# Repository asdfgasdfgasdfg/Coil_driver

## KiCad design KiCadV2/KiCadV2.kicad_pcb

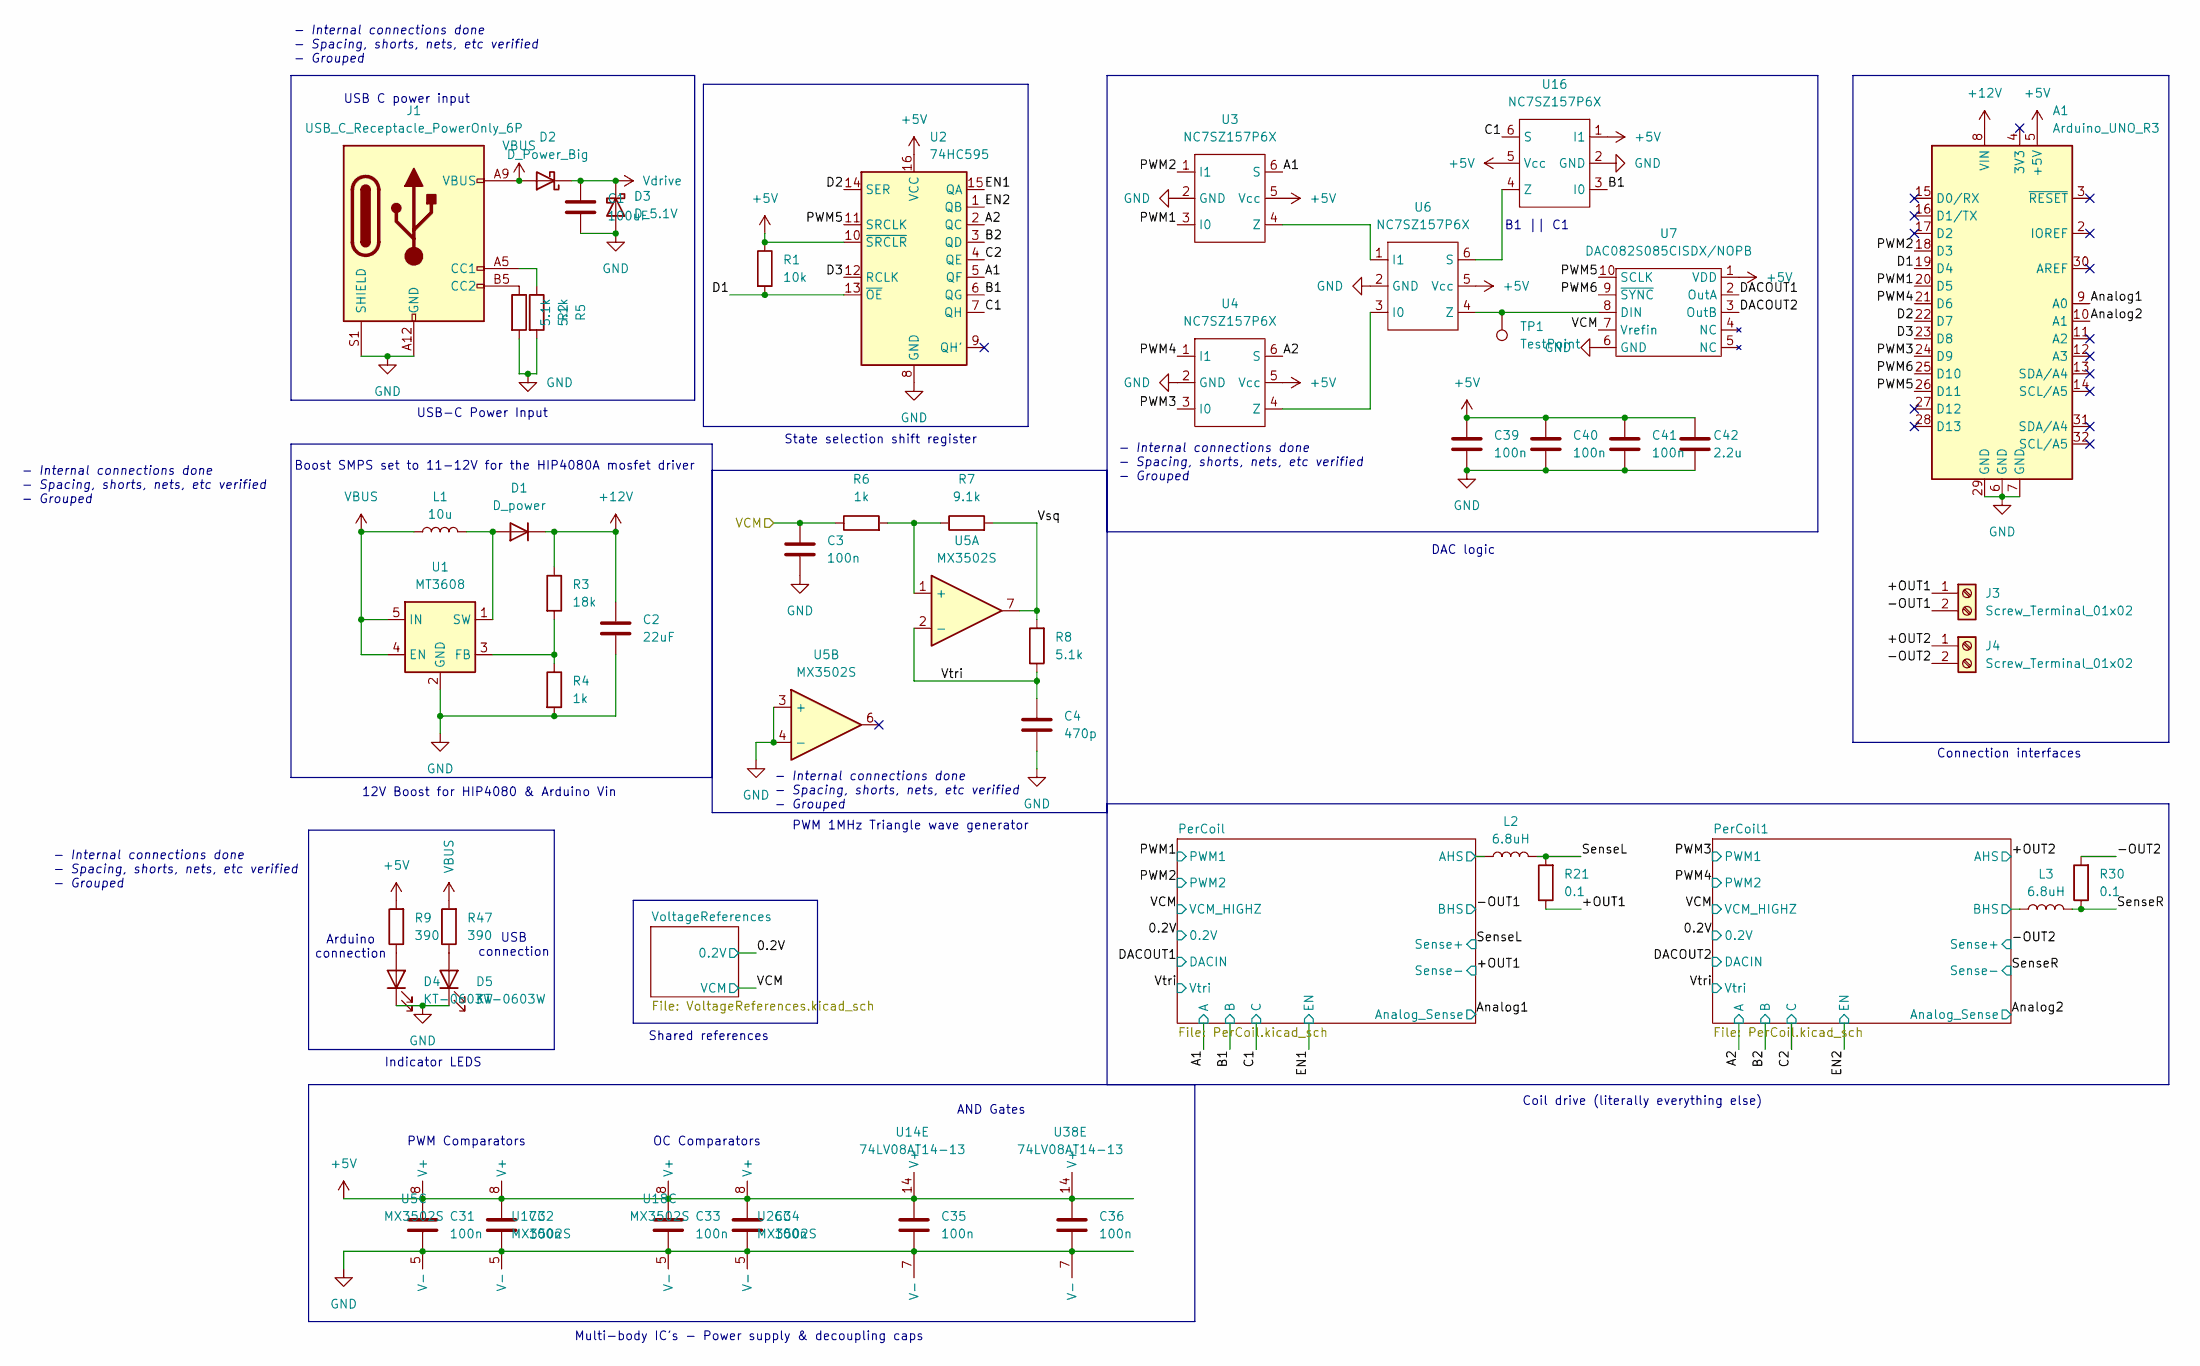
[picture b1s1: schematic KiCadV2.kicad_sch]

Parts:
A1: Arduino_UNO_R3; Arduino_UNO_R3_ConnOnly_Coil_Driver
C1: 100uF; C_1206_3216Metric; LCSC C15008
C2: 22uF; C_1206_3216Metric; LCSC C12891
C3, C31, C32, C33, C34, C35, C36, C39, C40, C41: 100n; C_0603_1608Metric; LCSC C14663
C4: 470p; C_0603_1608Metric; LCSC C396711
C42: 2.2u; C_0603_1608Metric; LCSC C23630
D1: D_power; D_SOD-123; LCSC C8598
D2: D_Power_Big; D_SMC; LCSC C18199212
D3: D_5.1V; D_SMB; LCSC C19077494
D4, D5: KT-0603W; LED_0603_1608Metric; LCSC C2290
J1: USB_C_Receptacle_PowerOnly_6P; USB_C_Receptacle_GCT_USB4135-GF-A_6P_TopMnt_Horizontal; LCSC C2927028
J3, J4: Screw_Terminal_01x02; PinHeader_2x01_P2.54mm_Vertical
L1: 10u; 10uH C15029; LCSC C15029
L2, L3: 6.8uH; 6.8uH C5127257; LCSC C5127257
R1: 10k; R_0603_1608Metric; LCSC C25804
R2, R5, R8: 5.1k; R_0603_1608Metric; LCSC C23186
R3: 18k; R_0603_1608Metric; LCSC C25810
R4, R6: 1k; R_0603_1608Metric; LCSC C21190
R7: 9.1k; R_0603_1608Metric; LCSC C23260
R9, R47: 390; R_0603_1608Metric; LCSC C23151
R21, R30: 0.1; R_1206_3216Metric; LCSC C42460614
TP1: TestPoint; TestPoint_Pad_D2.5mm
U1: MT3608; SOT-23-6; LCSC C84817
U2: 74HC595; SOIC-16_3.9x9.9mm_P1.27mm; LCSC C5947
U3, U4, U6, U16: NC7SZ157P6X; SOT-363_SC-70-6; LCSC C77686
U5, U17, U18, U26: MX3502S; SOP-8_3.76x4.96mm_P1.27mm; LCSC C19269867
U7: DAC082S085CISDX/NOPB; WSON-10-1_3x3mm_P0.5mm_1.6x2mm; LCSC C1555068
U14, U38: 74LV08AT14-13; TSSOP-14_4.4x5mm_P0.65mm; LCSC C842475

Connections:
+5V: A1.5 (+5V), C31.1, C32.1, C33.1, C34.1, C35.1, C36.1, C39.1, C40.1, C41.1, C42.1, R1.1, R9.2, U2.10 (~SRCLR), U2.16 (VCC), U3.5 (Vcc), U4.5 (Vcc), U5.8 (V+), U6.5 (Vcc), U7.1 (VDD), U14.14 (V+), U16.1 (I1), U16.5 (Vcc), U17.8 (V+), U18.8 (V+), U26.8 (V+), U38.14 (V+); also elsewhere on the board
+12V: A1.8 (VIN), C2.1, D1.1 (K), R3.1; also elsewhere on the board
/+OUT1: J3.1, R21.1; also elsewhere on the board
/+OUT2: J4.1; also elsewhere on the board
/-OUT1: J3.2; also elsewhere on the board
/-OUT2: J4.2, R30.2; also elsewhere on the board
/A1: U2.5 (QF), U3.6 (S); also elsewhere on the board
/A2: U2.2 (QC), U4.6 (S); also elsewhere on the board
/Analog1: A1.9 (A0); also elsewhere on the board
/Analog2: A1.10 (A1); also elsewhere on the board
/B1: U2.6 (QG), U16.3 (I0); also elsewhere on the board
/B2: U2.3 (QD); also elsewhere on the board
/C1: U2.7 (QH), U16.6 (S); also elsewhere on the board
/C2: U2.4 (QE); also elsewhere on the board
/D1: A1.19 (D4), R1.2, U2.13 (~OE)
/D2: A1.22 (D7), U2.14 (SER)
/D3: A1.23 (D8), U2.12 (RCLK)
/DACOUT1: U7.2 (OutA); also elsewhere on the board
/DACOUT2: U7.3 (OutB); also elsewhere on the board
/EN1: U2.15 (QA); also elsewhere on the board
/EN2: U2.1 (QB); also elsewhere on the board
/PWM1: A1.20 (D5), U3.3 (I0); also elsewhere on the board
/PWM2: A1.18 (D3), U3.1 (I1); also elsewhere on the board
/PWM3: A1.24 (D9), U4.3 (I0); also elsewhere on the board
/PWM4: A1.21 (D6), U4.1 (I1); also elsewhere on the board
/PWM5: A1.26 (D11), U2.11 (SRCLK), U7.10 (SCLK)
/PWM6: A1.25 (D10), U7.9 (~SYNC)
/PerCoil1/BHS: L3.1; also elsewhere on the board
/PerCoil1/SignalProcessingChain/HF PWM: U17.6; also elsewhere on the board
/PerCoil1/~OC1: U38.9 (B); also elsewhere on the board
/PerCoil/AHS: L2.1; also elsewhere on the board
/PerCoil/~OC1: U14.9 (B); also elsewhere on the board
/SenseL: L2.2, R21.2; also elsewhere on the board
/SenseR: L3.2, R30.1; also elsewhere on the board
/VCM: C3.1, R6.1, U7.7 (Vrefin); also elsewhere on the board
/Vsq: R7.2, R8.2, U5.7
/Vtri: C4.1, R8.1, U5.2 (-), U17.4 (-); also elsewhere on the board
GND: A1.6 (GND), A1.7 (GND), A1.29 (GND), C1.2, C2.2, C3.2, C4.2, C31.2, C32.2, C33.2, C34.2, C35.2, C36.2, C39.2, C40.2, C41.2, C42.2, D3.2 (A), D4.1 (K), D5.1 (K), J1.A12 (GND), J1.B12 (GND), J1.S1 (SHIELD), R2.2, R4.2, R5.2, U1.2 (GND), U2.8 (GND), U3.2 (GND), U4.2 (GND), U5.3 (+), U5.4 (-), U5.5 (V-), U6.2 (GND), U7.6 (GND), U14.7 (V-), U16.2 (GND), U17.5 (V-), U18.5 (V-), U26.5 (V-), U38.7 (V-); also elsewhere on the board
unnamed: D1.2 (A), L1.2, U1.1 (SW)
unnamed: D4.2 (A), R9.1
unnamed: D5.2 (A), R47.1
unnamed: J1.A5 (CC1), R5.1
unnamed: J1.B5 (CC2), R2.1
unnamed: R3.2, R4.1, U1.3 (FB)
unnamed: U3.4 (Z), U6.1 (I1)
unnamed: U4.4 (Z), U6.3 (I0)
unnamed: R6.2, R7.1, U5.1 (+)
unnamed: TP1.1, U6.4 (Z), U7.8 (DIN)
unnamed: U6.6 (S), U16.4 (Z)
unnamed 91: U17.3 (+); also elsewhere on the board
VBUS: D2.2 (A), J1.A9 (VBUS), J1.B9 (VBUS), L1.1, R47.2, U1.4 (EN), U1.5 (IN); also elsewhere on the board
Vdrive: C1.1, D2.1 (K), D3.1 (K); also elsewhere on the board

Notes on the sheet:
AND Gates
- Internal connections done - Spacing, shorts, nets, etc verified - Grouped
12V Boost for HIP4080 & Arduino Vin
PWM 1MHz Triangle wave generator
State selection shift register
DAC logic
Shared references
PWM Comparators
Boost SMPS set to 11-12V for the HIP4080A mosfet driver
OC Comparators
Indicator LEDS
USB connection
B1 || C1
Arduino connection
Connection interfaces
USB-C Power Input
Multi-body IC's - Power supply & decoupling caps
USB C power input
Coil drive (literally everything else)

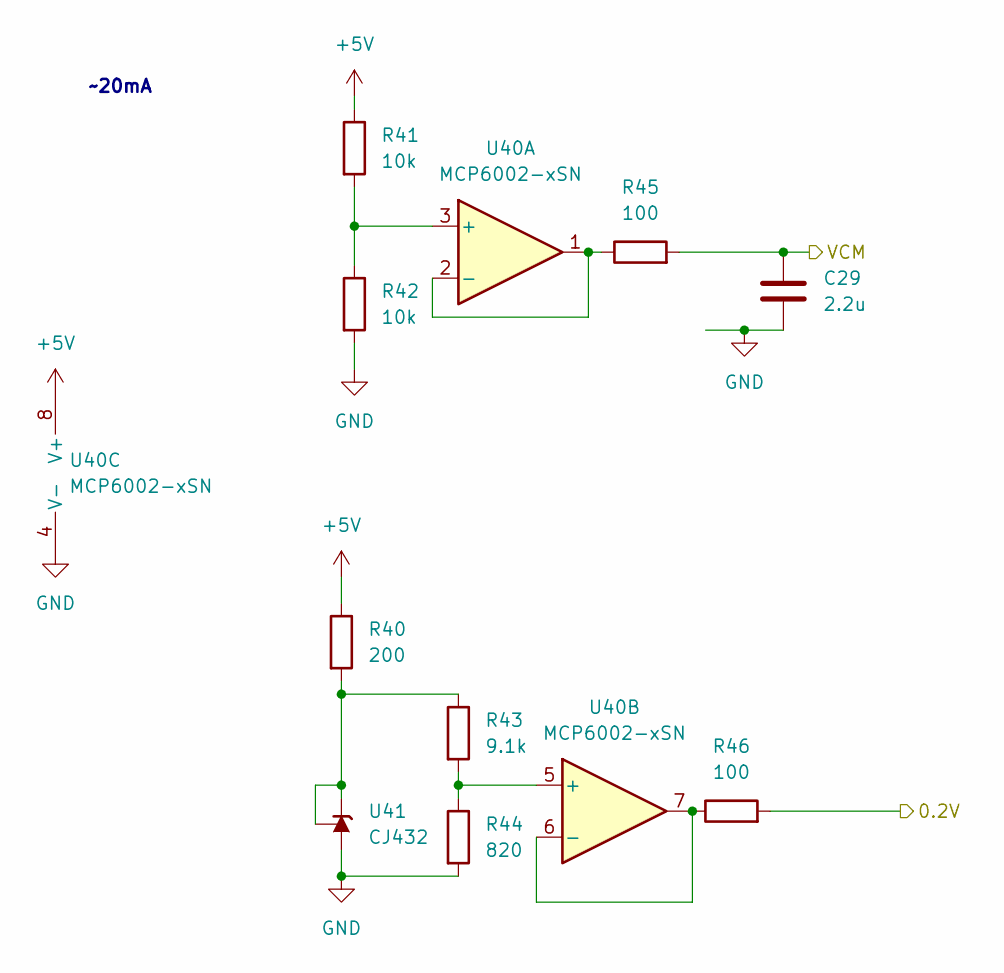
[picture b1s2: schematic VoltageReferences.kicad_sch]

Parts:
C29: 2.2u; C_0603_1608Metric; LCSC C23630
R40: 200; R_0805_2012Metric; LCSC C17540
R41, R42: 10k; R_0603_1608Metric; LCSC C25804
R43: 9.1k; R_0603_1608Metric; LCSC C23260
R44: 820; R_0603_1608Metric; LCSC C23253
R45, R46: 100; R_0603_1608Metric; LCSC C22775
U40: MCP6002-xSN; SOIC-8_3.9x4.9mm_P1.27mm; LCSC C7377
U41: CJ432; SOT-23; LCSC C3113

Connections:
+5V: R40.1, R41.1, U40.8 (V+); also elsewhere on the board
/0.2V: R46.2; also elsewhere on the board
/VCM: C29.2, R45.2; also elsewhere on the board
GND: C29.1, R42.2, R44.2, U40.4 (V-), U41.3 (A); also elsewhere on the board
unnamed: R41.2, R42.1, U40.3 (+)
unnamed: R45.1, U40.1, U40.2 (-)
unnamed: R43.2, R44.1, U40.5 (+)
unnamed: R46.1, U40.6 (-), U40.7
unnamed: R40.2, R43.1, U41.1 (REF), U41.2 (K)

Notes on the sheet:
~20mA

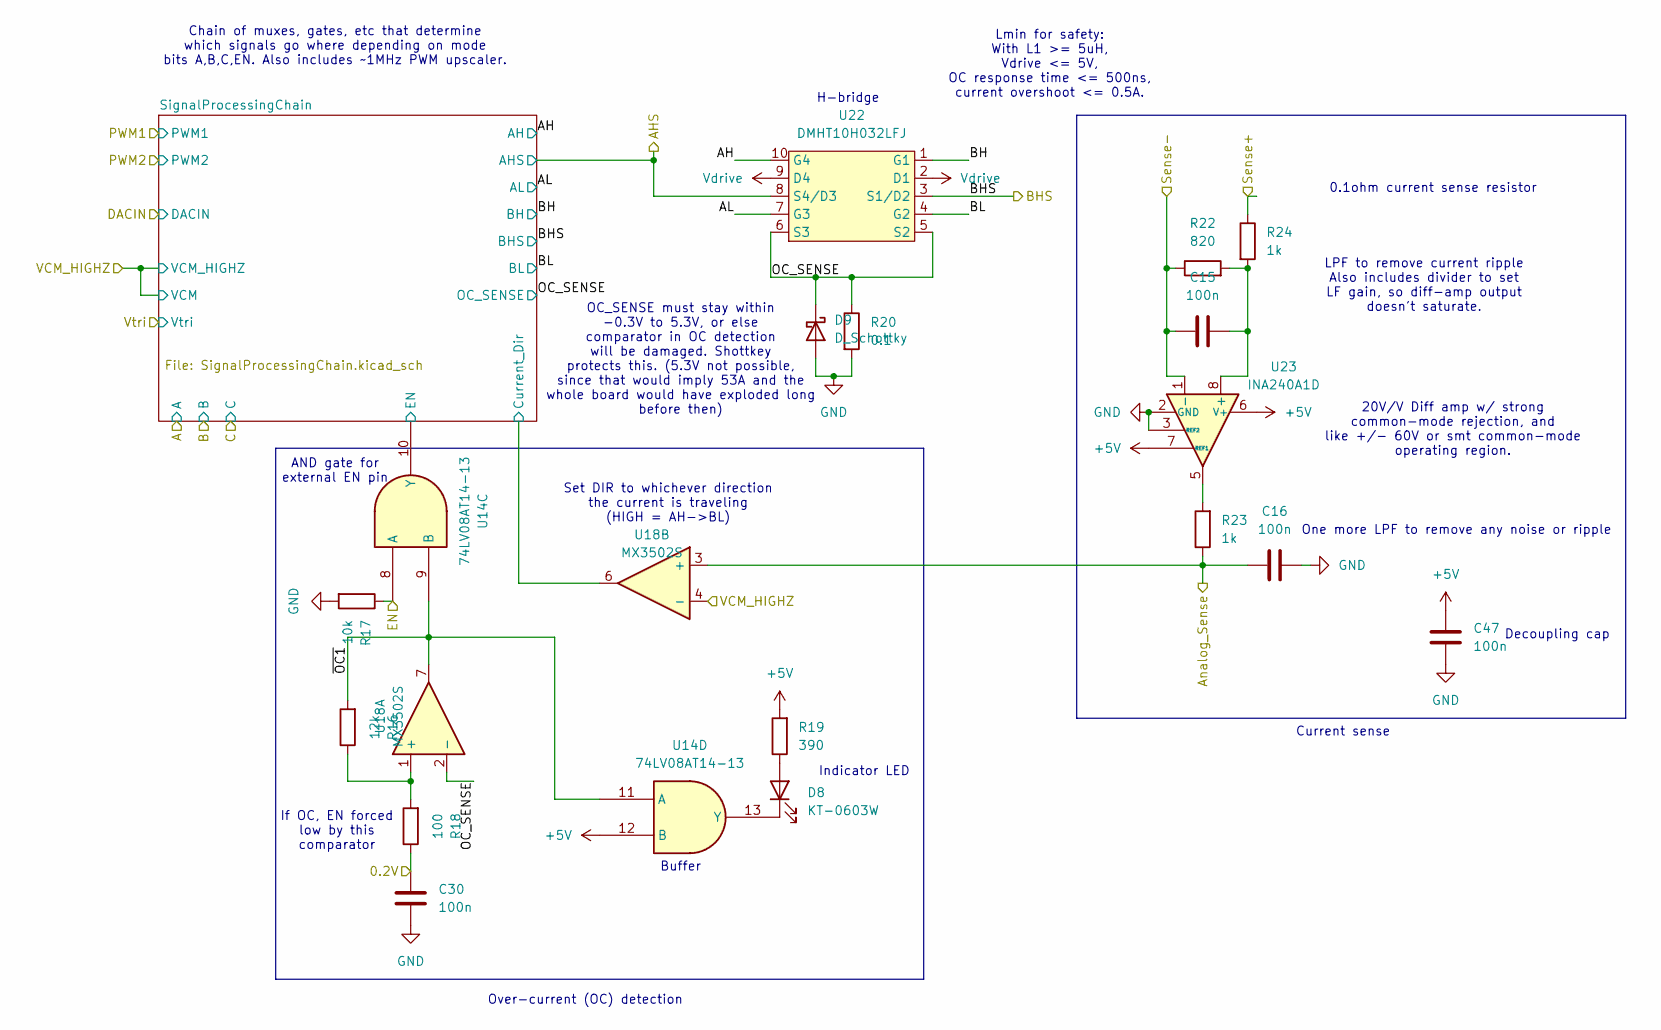
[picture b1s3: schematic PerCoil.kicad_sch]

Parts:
C15, C16, C30, C47: 100n; C_0603_1608Metric; LCSC C14663
D8: KT-0603W; LED_0603_1608Metric; LCSC C2290
D9: D_Schottky; D_SOD-323; LCSC C7420329
R16: 12k; R_0603_1608Metric; LCSC C22790
R17: 10k; R_0603_1608Metric; LCSC C25804
R18: 100; R_0603_1608Metric; LCSC C22775
R19: 390; R_0603_1608Metric; LCSC C23151
R20: 0.1; R_1206_3216Metric; LCSC C42460614
R22: 820; R_0603_1608Metric; LCSC C23253
R23, R24: 1k; R_0603_1608Metric; LCSC C21190
U14: 74LV08AT14-13; TSSOP-14_4.4x5mm_P0.65mm; LCSC C842475
U18: MX3502S; SOP-8_3.76x4.96mm_P1.27mm; LCSC C19269867
U22: DMHT10H032LFJ; V-DFN5045-12
U23: INA240A1D; SOIC-8_3.9x4.9mm_P1.27mm; LCSC C2060769

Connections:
+5V: C47.1, R19.2, U14.12 (B), U23.6 (V+), U23.7 (REF1); also elsewhere on the board
/0.2V: C30.2, R18.1; also elsewhere on the board
/+OUT1: C15.1, R22.1, U23.1 (-); also elsewhere on the board
/-OUT1: U22.3 (S1/D2); also elsewhere on the board
/Analog1: C16.2, R23.1, U18.3 (+); also elsewhere on the board
/EN1: R17.1, U14.8 (A); also elsewhere on the board
/PerCoil/AH: U22.10 (G4); also elsewhere on the board
/PerCoil/AHS: U22.8 (S4/D3); also elsewhere on the board
/PerCoil/AL: U22.7 (G3); also elsewhere on the board
/PerCoil/BH: U22.1 (G1); also elsewhere on the board
/PerCoil/BL: U22.4 (G2); also elsewhere on the board
/PerCoil/OC_SENSE: D9.1 (K), R20.1, U18.2 (-), U22.5 (S2), U22.6 (S3); also elsewhere on the board
/PerCoil/SignalProcessingChain/Current_Dir: U18.6; also elsewhere on the board
/PerCoil/SignalProcessingChain/EN: U14.10 (Y); also elsewhere on the board
/PerCoil/~OC1: R16.2, U14.9 (B), U14.11 (A), U18.7
/SenseL: R24.1; also elsewhere on the board
/VCM: U18.4 (-); also elsewhere on the board
GND: C16.1, C30.1, C47.2, D9.2 (A), R17.2, R20.2, U23.2 (GND), U23.3 (REF2), U23.4 (GND); also elsewhere on the board
unnamed: D8.2 (A), R19.1
unnamed: D8.1 (K), U14.13 (Y)
unnamed: R23.2, U23.5
unnamed: R16.1, R18.2, U18.1 (+)
unnamed: C15.2, R22.2, R24.2, U23.8 (+)
Vdrive: U22.2 (D1), U22.9 (D4); also elsewhere on the board

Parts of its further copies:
C17, C18, C48, C49: 100n; C_0603_1608Metric; LCSC C14663
D10: KT-0603W; LED_0603_1608Metric; LCSC C2290
D11: D_Schottky; D_SOD-323; LCSC C7420329
R25: 12k; R_0603_1608Metric; LCSC C22790
R26: 10k; R_0603_1608Metric; LCSC C25804
R27: 100; R_0603_1608Metric; LCSC C22775
R28: 390; R_0603_1608Metric; LCSC C23151
R29: 0.1; R_1206_3216Metric; LCSC C42460614
R31: 820; R_0603_1608Metric; LCSC C23253
R32, R33: 1k; R_0603_1608Metric; LCSC C21190
U30: DMHT10H032LFJ; V-DFN5045-12
U31: INA240A1D; SOIC-8_3.9x4.9mm_P1.27mm; LCSC C2060769

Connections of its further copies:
+5V: C48.1, R28.2, U31.6 (V+), U31.7 (REF1); also elsewhere on the board
/0.2V: C49.2, R27.1; also elsewhere on the board
/+OUT2: U30.8 (S4/D3); also elsewhere on the board
/-OUT2: R33.1; also elsewhere on the board
/Analog2: C18.2, R32.1; also elsewhere on the board
/EN2: R26.1; also elsewhere on the board
/PerCoil1/AH: U30.10 (G4); also elsewhere on the board
/PerCoil1/AL: U30.7 (G3); also elsewhere on the board
/PerCoil1/BH: U30.1 (G1); also elsewhere on the board
/PerCoil1/BHS: U30.3 (S1/D2); also elsewhere on the board
/PerCoil1/BL: U30.4 (G2); also elsewhere on the board
/PerCoil1/OC_SENSE: D11.1 (K), R29.1, U30.5 (S2), U30.6 (S3); also elsewhere on the board
/PerCoil1/~OC1: R25.2; also elsewhere on the board
/SenseR: C17.1, R31.1, U31.1 (-); also elsewhere on the board
GND: C18.1, C48.2, C49.1, D11.2 (A), R26.2, R29.2, U31.2 (GND), U31.3 (REF2), U31.4 (GND); also elsewhere on the board
unnamed: D10.2 (A), R28.1
unnamed 70: D10.1 (K); also elsewhere on the board
unnamed: R32.2, U31.5
unnamed 94: R25.1, R27.2; also elsewhere on the board
unnamed: C17.2, R31.2, R33.2, U31.8 (+)
Vdrive: U30.2 (D1), U30.9 (D4); also elsewhere on the board

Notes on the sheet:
Chain of muxes, gates, etc that determine which signals go where depending on mode bits A,B,C,EN. Also includes ~1MHz PWM upscaler.
If OC, EN forced low by this comparator
H-bridge
OC_SENSE must stay within -0.3V to 5.3V, or else comparator in OC detection will be damaged. Shottkey protects this. (5.3V not possible, since that would imply 53A and the whole board would have exploded long before then)
20V/V Diff amp w/ strong common-mode rejection, and like +/- 60V or smt common-mode operating region.
Decoupling cap
Buffer
One more LPF to remove any noise or ripple
Set DIR to whichever direction the current is traveling (HIGH = AH->BL)
LPF to remove current ripple Also includes divider to set LF gain, so diff-amp output doesn't saturate.
AND gate for external EN pin
Lmin for safety: With L1 >= 5uH, Vdrive <= 5V, OC response time <= 500ns, current overshoot <= 0.5A.
Over-current (OC) detection
Indicator LED
0.1ohm current sense resistor
Current sense

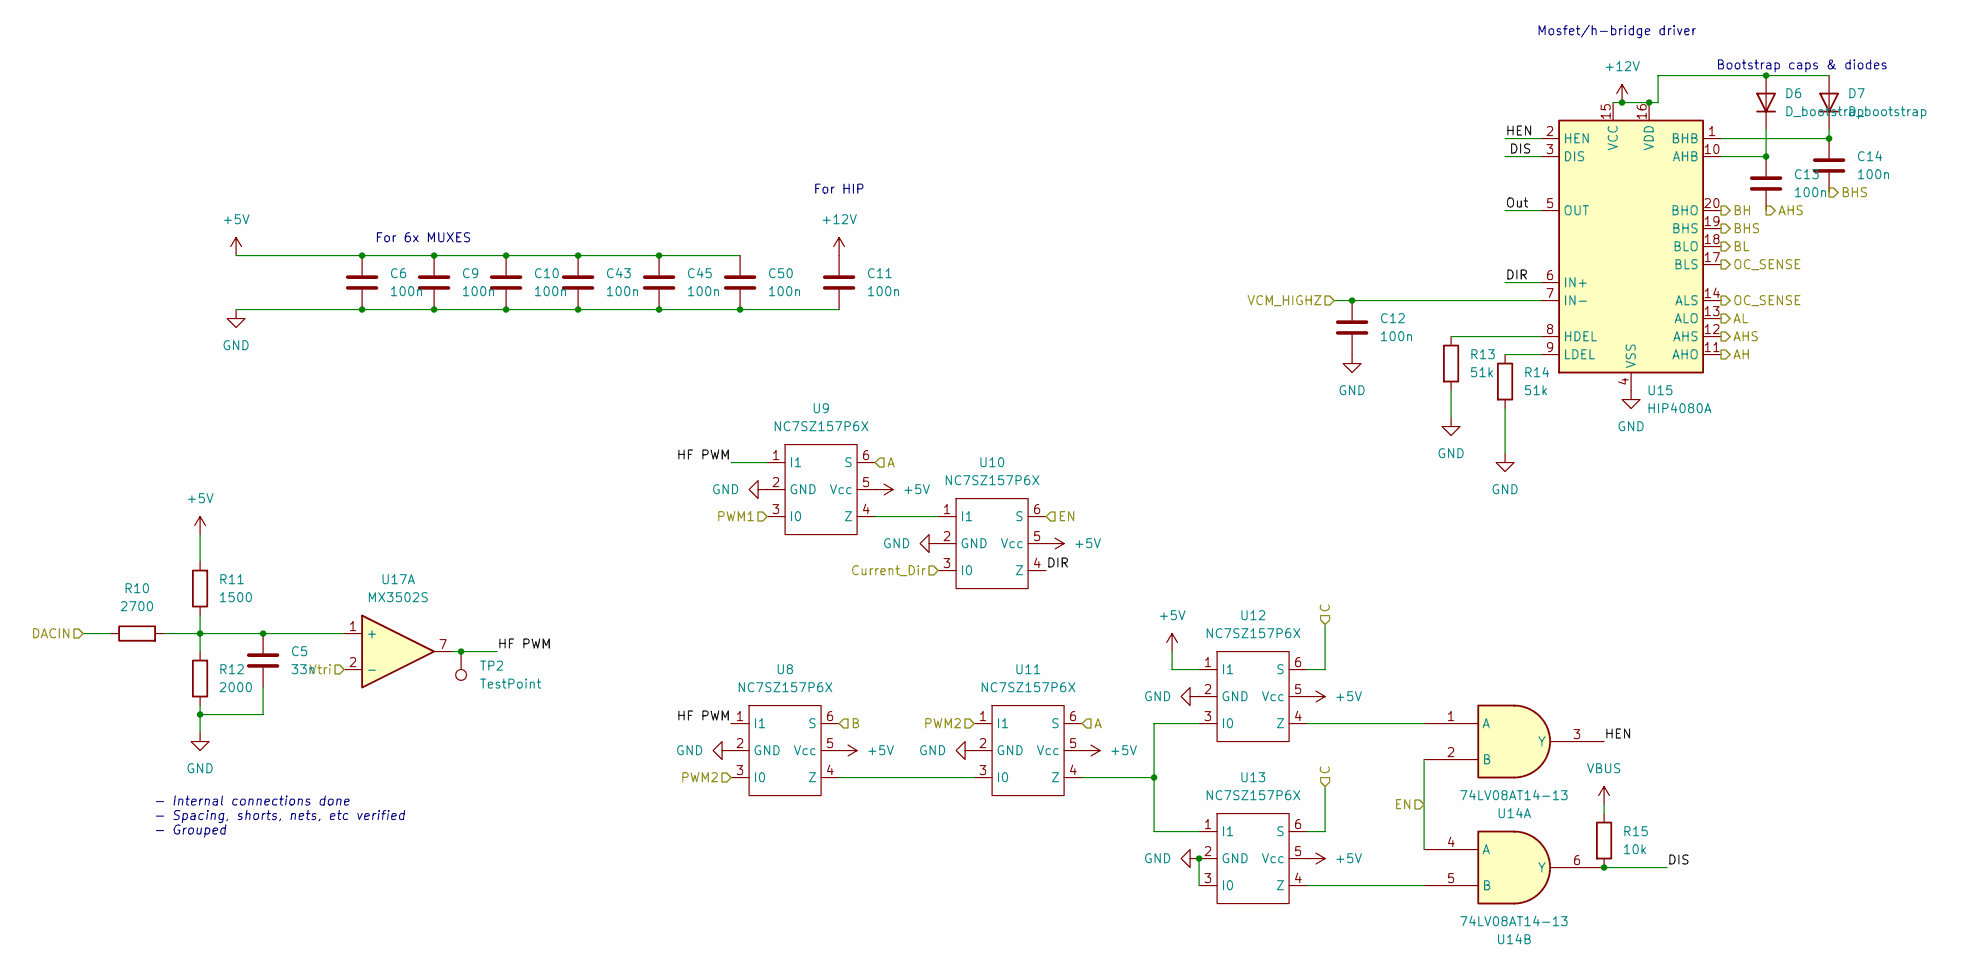
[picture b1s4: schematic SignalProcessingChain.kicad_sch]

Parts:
C5: 33n; C_0603_1608Metric; LCSC C21117
C6, C9, C10, C11, C12, C13, C14, C43, C45, C50: 100n; C_0603_1608Metric; LCSC C14663
D6, D7: D_bootstrap; D_SOD-523; LCSC C7502714
R10: 2700; R_0603_1608Metric; LCSC C13167
R11: 1500; R_0603_1608Metric; LCSC C22843
R12: 2000; R_0603_1608Metric; LCSC C22975
R13, R14: 51k; R_0603_1608Metric; LCSC C23196
R15: 10k; R_0603_1608Metric; LCSC C25804
TP2: TestPoint; TestPoint_Pad_D2.5mm
U8, U9, U10, U11, U12, U13: NC7SZ157P6X; SOT-363_SC-70-6; LCSC C77686
U14: 74LV08AT14-13; TSSOP-14_4.4x5mm_P0.65mm; LCSC C842475
U15: HIP4080A; SOIC-20W_7.5x12.8mm_P1.27mm
U17: MX3502S; SOP-8_3.76x4.96mm_P1.27mm; LCSC C19269867

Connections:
+5V: C6.1, C9.1, C10.1, C43.1, C45.1, C50.1, R11.2, U8.5 (Vcc), U9.5 (Vcc), U10.5 (Vcc), U11.5 (Vcc), U12.1 (I1), U12.5 (Vcc), U13.5 (Vcc); also elsewhere on the board
+12V: C11.1, D6.2 (A), D7.2 (A), U15.15 (VCC), U15.16 (VDD); also elsewhere on the board
/-OUT1: C14.2, U15.19 (BHS); also elsewhere on the board
/A1: U9.6 (S), U11.6 (S); also elsewhere on the board
/B1: U8.6 (S); also elsewhere on the board
/C1: U12.6 (S), U13.6 (S); also elsewhere on the board
/DACOUT1: R10.1; also elsewhere on the board
/PWM1: U9.3 (I0); also elsewhere on the board
/PWM2: U8.3 (I0), U11.1 (I1); also elsewhere on the board
/PerCoil1/SignalProcessingChain/HF PWM: U17.6; also elsewhere on the board
/PerCoil/AH: U15.11 (AHO); also elsewhere on the board
/PerCoil/AHS: C13.2, U15.12 (AHS); also elsewhere on the board
/PerCoil/AL: U15.13 (ALO); also elsewhere on the board
/PerCoil/BH: U15.20 (BHO); also elsewhere on the board
/PerCoil/BL: U15.18 (BLO); also elsewhere on the board
/PerCoil/OC_SENSE: U15.14 (ALS), U15.17 (BLS); also elsewhere on the board
/PerCoil/SignalProcessingChain/Current_Dir: U10.3 (I0); also elsewhere on the board
/PerCoil/SignalProcessingChain/DIR: U10.4 (Z), U15.6 (IN+)
/PerCoil/SignalProcessingChain/DIS: R15.2, U14.6 (Y), U15.3 (DIS)
/PerCoil/SignalProcessingChain/EN: U10.6 (S), U14.2 (B), U14.4 (A); also elsewhere on the board
/PerCoil/SignalProcessingChain/HEN: U14.3 (Y), U15.2 (HEN)
/PerCoil/SignalProcessingChain/HF PWM: TP2.1, U8.1 (I1), U9.1 (I1), U17.7
/PerCoil/SignalProcessingChain/Out: U15.5 (OUT)
/VCM: C12.1, U15.7 (IN-); also elsewhere on the board
/Vtri: U17.2 (-), U17.4 (-); also elsewhere on the board
GND: C5.2, C6.2, C9.2, C10.2, C11.2, C12.2, C43.2, C45.2, C50.2, R12.1, R13.2, R14.2, U8.2 (GND), U9.2 (GND), U10.2 (GND), U11.2 (GND), U12.2 (GND), U13.2 (GND), U13.3 (I0), U15.4 (VSS); also elsewhere on the board
unnamed: C13.1, D6.1 (K), U15.10 (AHB)
unnamed: C14.1, D7.1 (K), U15.1 (BHB)
unnamed: U9.4 (Z), U10.1 (I1)
unnamed: U8.4 (Z), U11.3 (I0)
unnamed: U11.4 (Z), U12.3 (I0), U13.1 (I1)
unnamed: U12.4 (Z), U14.1 (A)
unnamed: U13.4 (Z), U14.5 (B)
unnamed: R13.1, U15.8 (HDEL)
unnamed: R14.1, U15.9 (LDEL)
unnamed: C5.1, R10.2, R11.1, R12.2, U17.1 (+)
unnamed 91: U17.3 (+); also elsewhere on the board
VBUS: R15.1; also elsewhere on the board

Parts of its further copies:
C7, C23, C24, C25, C26, C27, C28, C44, C46, C51: 100n; C_0603_1608Metric; LCSC C14663
C19: 33n; C_0603_1608Metric; LCSC C21117
D12, D13: D_bootstrap; D_SOD-523; LCSC C7502714
R34: 2700; R_0603_1608Metric; LCSC C13167
R35: 1500; R_0603_1608Metric; LCSC C22843
R36: 2000; R_0603_1608Metric; LCSC C22975
R37, R38: 51k; R_0603_1608Metric; LCSC C23196
R39: 10k; R_0603_1608Metric; LCSC C25804
TP3: TestPoint; TestPoint_Pad_D2.5mm
U32, U33, U34, U35, U36, U37: NC7SZ157P6X; SOT-363_SC-70-6; LCSC C77686
U39: HIP4080A; SOIC-20W_7.5x12.8mm_P1.27mm

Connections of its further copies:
+5V: C7.1, C23.1, C24.1, C44.1, C46.1, C51.1, R35.2, U32.5 (Vcc), U33.5 (Vcc), U34.5 (Vcc), U35.5 (Vcc), U36.1 (I1), U36.5 (Vcc), U37.5 (Vcc); also elsewhere on the board
+12V: C25.1, D12.2 (A), D13.2 (A), U39.15 (VCC), U39.16 (VDD); also elsewhere on the board
/+OUT2: C27.2, U39.12 (AHS); also elsewhere on the board
/A2: U33.6 (S), U35.6 (S); also elsewhere on the board
/B2: U32.6 (S); also elsewhere on the board
/C2: U36.6 (S), U37.6 (S); also elsewhere on the board
/DACOUT2: R34.1; also elsewhere on the board
/PWM3: U33.3 (I0); also elsewhere on the board
/PWM4: U32.3 (I0), U35.1 (I1); also elsewhere on the board
/PerCoil1/AH: U39.11 (AHO); also elsewhere on the board
/PerCoil1/AL: U39.13 (ALO); also elsewhere on the board
/PerCoil1/BH: U39.20 (BHO); also elsewhere on the board
/PerCoil1/BHS: C28.2, U39.19 (BHS); also elsewhere on the board
/PerCoil1/BL: U39.18 (BLO); also elsewhere on the board
/PerCoil1/OC_SENSE: U39.14 (ALS), U39.17 (BLS); also elsewhere on the board
/PerCoil1/SignalProcessingChain/Current_Dir: U34.3 (I0); also elsewhere on the board
/PerCoil1/SignalProcessingChain/DIR: U34.4 (Z), U39.6 (IN+)
/PerCoil1/SignalProcessingChain/DIS: R39.2, U39.3 (DIS); also elsewhere on the board
/PerCoil1/SignalProcessingChain/EN: U34.6 (S); also elsewhere on the board
/PerCoil1/SignalProcessingChain/HEN: U39.2 (HEN); also elsewhere on the board
/PerCoil1/SignalProcessingChain/HF PWM: TP3.1, U32.1 (I1), U33.1 (I1); also elsewhere on the board
/PerCoil1/SignalProcessingChain/Out: U39.5 (OUT)
/VCM: C26.1, U39.7 (IN-); also elsewhere on the board
GND: C7.2, C19.2, C23.2, C24.2, C25.2, C26.2, C44.2, C46.2, C51.2, R36.1, R37.2, R38.2, U32.2 (GND), U33.2 (GND), U34.2 (GND), U35.2 (GND), U36.2 (GND), U37.2 (GND), U37.3 (I0), U39.4 (VSS); also elsewhere on the board
unnamed: C27.1, D12.1 (K), U39.10 (AHB)
unnamed: C28.1, D13.1 (K), U39.1 (BHB)
unnamed 91: C19.1, R34.2, R35.1, R36.2; also elsewhere on the board
unnamed: U32.4 (Z), U35.3 (I0)
unnamed: U33.4 (Z), U34.1 (I1)
unnamed: U35.4 (Z), U36.3 (I0), U37.1 (I1)
unnamed 99: U36.4 (Z); also elsewhere on the board
unnamed 100: U37.4 (Z); also elsewhere on the board
unnamed: R37.1, U39.8 (HDEL)
unnamed: R38.1, U39.9 (LDEL)
VBUS: R39.1; also elsewhere on the board

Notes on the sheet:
For 6x MUXES
Mosfet/h-bridge driver
- Internal connections done - Spacing, shorts, nets, etc verified - Grouped
Bootstrap caps & diodes
For HIP

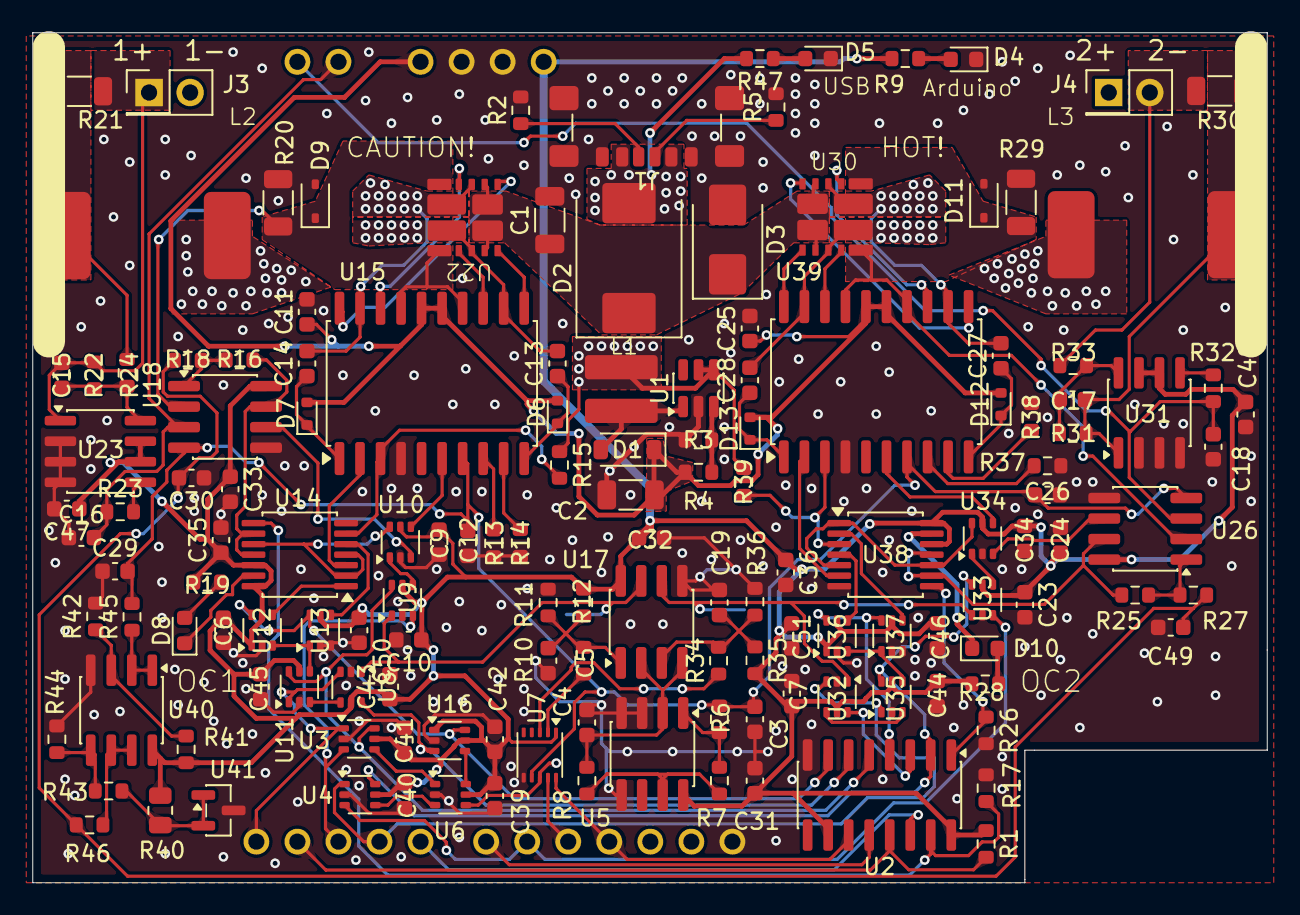
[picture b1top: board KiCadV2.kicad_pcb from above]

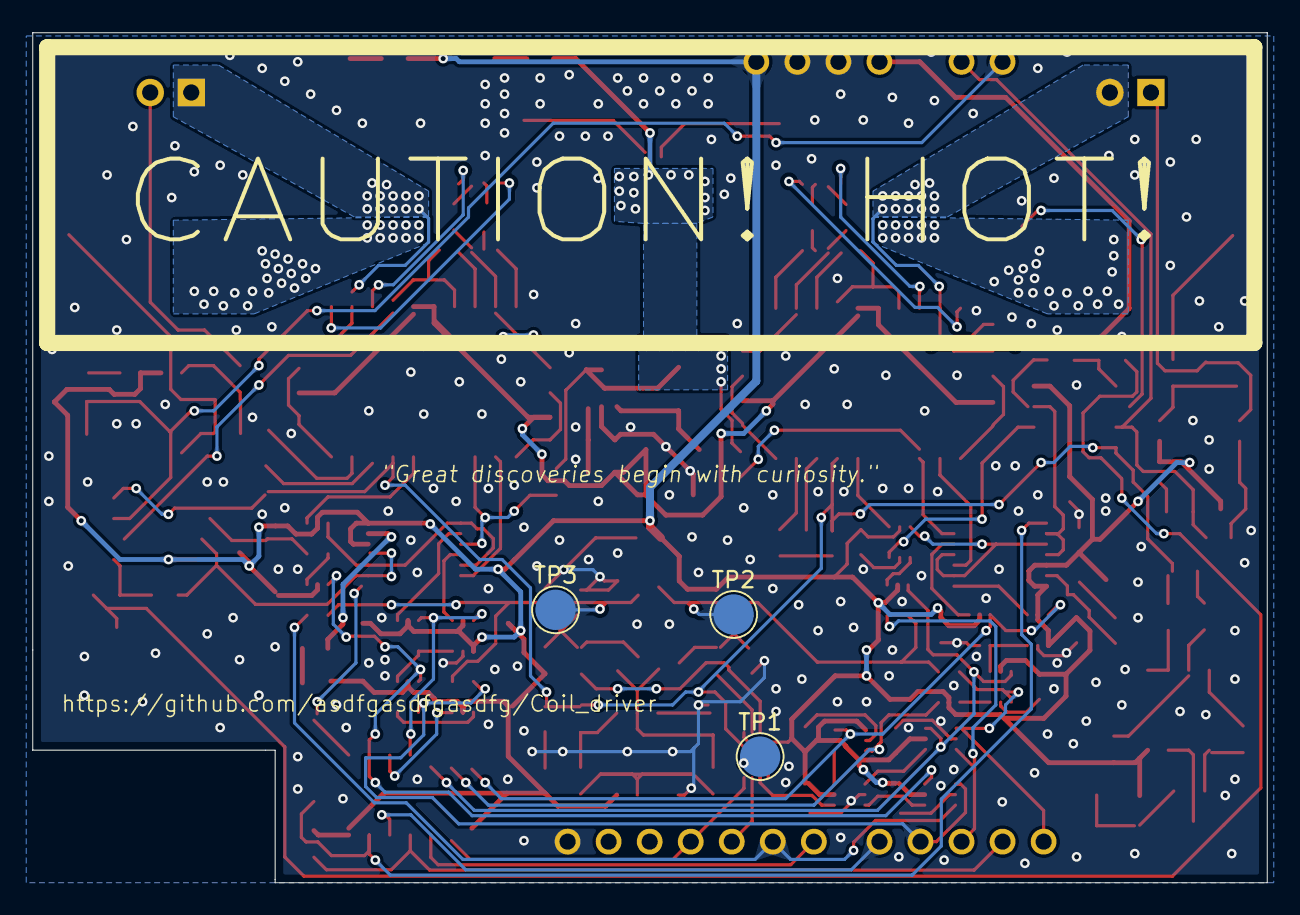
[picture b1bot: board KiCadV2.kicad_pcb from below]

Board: 2 copper layers, 76.4 x 52.6 mm, 148 parts (4 on the bottom side), 108 nets.

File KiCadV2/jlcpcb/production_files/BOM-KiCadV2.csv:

Comment,Designator,Footprint,LCSC,Quantity
0.1,"R20,R21,R29,R30",R_1206_3216Metric,C42460614,4
100,"R18,R27,R45,R46",R_0603_1608Metric,C22775,4
100n,"C10,C11,C12,C13,C14,C15,C16,C17,C18,C23,C24,C25,C26,C27,C28,C3,C30,C31,C32,C33,C34,C35,C36,C39,C40,C41,C43,C44,C45,C46,C47,C48,C49,C50,C51,C6,C7,C9",C_0603_1608Metric,C14663,38
100uF,C1,C_1206_3216Metric,C15008,1
10k,"R1,R15,R17,R26,R39,R41,R42",R_0603_1608Metric,C25804,7
10u,L1,10uH C15029,C15029,1
12k,"R16,R25",R_0603_1608Metric,C22790,2
1500,"R11,R35",R_0603_1608Metric,C22843,2
18k,R3,R_0603_1608Metric,C25810,1
1k,"R23,R24,R32,R33,R4,R6",R_0603_1608Metric,C21190,6
2.2u,"C29,C42",C_0603_1608Metric,C23630,2
200,R40,R_0805_2012Metric,C17540,1
2000,"R12,R36",R_0603_1608Metric,C22975,2
22uF,C2,C_1206_3216Metric,C12891,1
2700,"R10,R34",R_0603_1608Metric,C13167,2
33n,"C19,C5",C_0603_1608Metric,C21117,2
390,"R19,R28,R47,R9",R_0603_1608Metric,C23151,4
470p,C4,C_0603_1608Metric,C396711,1
5.1k,"R2,R5,R8",R_0603_1608Metric,C23186,3
51k,"R13,R14,R37,R38",R_0603_1608Metric,C23196,4
6.8uH,"L2,L3",6.8uH C5127257,C5127257,2
74HC595,U2,SOIC-16_3.9x9.9mm_P1.27mm,C5947,1
74LV08AT14-13,"U14,U38",TSSOP-14_4.4x5mm_P0.65mm,C842475,2
820,"R22,R31,R44",R_0603_1608Metric,C23253,3
9.1k,"R43,R7",R_0603_1608Metric,C23260,2
CJ432,U41,SOT-23,C3113,1
DAC082S085CISDX/NOPB,U7,WSON-10-1_3x3mm_P0.5mm_1.6x2mm,C1555068,1
D_5.1V,D3,D_SMB,C19077494,1
D_Power_Big,D2,D_SMC,C18199212,1
D_Schottky,"D11,D9",D_SOD-323,C7420329,2
D_bootstrap,"D12,D13,D6,D7",D_SOD-523,C7502714,4
D_power,D1,D_SOD-123,C8598,1
INA240A1D,"U23,U31",SOIC-8_3.9x4.9mm_P1.27mm,C2060769,2
KT-0603W,"D10,D4,D5,D8",LED_0603_1608Metric,C2290,4
MCP6002-xSN,U40,SOIC-8_3.9x4.9mm_P1.27mm,C7377,1
MT3608,U1,SOT-23-6,C84817,1
MX3502S,"U17,U18,U26,U5",SOP-8_3.76x4.96mm_P1.27mm,C19269867,4
NC7SZ157P6X,"U10,U11,U12,U13,U16,U3,U32,U33,U34,U35,U36,U37,U4,U6,U8,U9",SOT-363_SC-70-6,C77686,16
USB_C_Receptacle_PowerOnly_6P,J1,USB_C_Receptacle_GCT_USB4135-GF-A_6P_TopMnt_Horizontal,C2927028,1
